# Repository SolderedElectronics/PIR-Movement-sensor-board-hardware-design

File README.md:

# PIR Movement sensor board Hardware Design

## About the Product

|  |
| :----------------------------------------------------------: |
| [Buy PIR Movement sensor board](https://www.solde.red/333083) |

A PIR (passive infrared) motion sensor is a device that detects physical movement within its field of vision by sensing changes in infrared radiation. This sensor works on the principle of detecting thermal thermal signals emitted by objects, mainly warm-blooded creatures like humans. The “passive” in the name refers to the fact that the sensor itself does not emit or radiate any energy for detection.

Easily connects to Dasduino/Arduino via digital pin. When it detects movement, it sets the output digital pin to HIGH. The angle that the sensor “sees” is 100 degrees and reaches up to 5 meters. It has a potentiometer for delay (how often to check for movement).

It is often used in a variety of applications, including home security systems, automatic lighting, and energy management, among others.

---

## Repository Contents

This repository contains all design files for PIR Movement sensor board, organized as follows:

- **`CAD` folder**: Contains KiCAD design files, including:
  - Schematics
  - PCB layout
  - Panel PCB layout
  - Source 3D files in Fusion360, if any
  - All files are sorted by version with a detailed change log.
- **`OUTPUTS` folder**: Includes all production-ready files, such as:
  - Bill of Materials (BOM) and interactive BOM (iBOM)
  - PDF versions of schematics
  - 3D `.step` file of the board
  - 3D-printable models
  - Gerber files for PCB manufacturing
  - Image of the pinout of the board
  - Product image
  - Compliance, legal and generic sales documents

Refer to the `Change Log` in the CAD folder for details about updates between versions.

---

## Learn More About the Product

Beyond the repository, explore the following resources:

### Soldered Verify

The **Soldered Verify** system ensures every board you purchase from Soldered is fully functional. It also provides access to exclusive test data for your product. To get started, find the unique Soldered Verify ID on your product's packaging and enter the ID on the [Soldered Verify page](https://soldered.com/verify/) to access test results and additional product details.

### Soldered Community

Soldered Community is your go-to place for technical support. Our engineers track and answer all questions posted there, and it’s a great space for the maker community. Get answers to your questions and solutions for your challenges at [Soldered Community](https://soldered.com/community).

### solde.red

solde.red is an ultimate URL shortener and information hub. Access it by typing solde.red/ followed by your product SKU, e.g., [solde.red/333000](https://solde.red/333000), to find getting-started guides, datasheets, open-source hardware and software files, certifications, images, pinouts, and more. Read more about the shortener [here](https://solde.red/info/).

---

## Contributing

Contributions are welcome! Here’s how you can get involved:

- Submit pull requests to enhance the design or fix issues.
- Report bugs or problems by opening an issue.

We encourage community collaboration to make this product even better.

---

## About Soldered

[Soldered for Makers](https://soldered.com) specializes in designing and manufacturing electronic products tailored for enthusiasts, ranging from hobbyists to professionals. Our portfolio includes electronic boards, sensors, and actuators that are widely utilized in fields such as microelectronics, mechatronics, robotics, programming, and IoT. Every product we offer is designed in-house and built upon open-source hardware and software platforms. Proudly certified and manufactured within the European Union, our catalog likely includes the product you need for your project.

We complement these products with comprehensive tutorials and manuals, product descriptions, schematics, programming codes, and project examples. Our round-the-clock [customer and technical support](https://soldered.com/community) is available for all our products, irrespective of the sales channel. Soldered’s success and services reflect our maker community’s unwavering [trust](https://www.trustpilot.com/review/soldered.com), for which we are deeply grateful. Join our community and create using Soldered products.

---

## License

All Soldered open-source hardware (OSH) is under The TAPR Open Hardware License. Read more in the LICENSE file located in this repository.

**Disclaimer:**

No warranty - all designs in this repository are distributed in the hope that they will be useful, but without any warranty. They are provided "AS IS", therefore without warranty of any kind, either expressed or implied. The entire quality and performance of what you do with the contents of this repository are your responsibility. In no event Soldered Electronics will be liable for your damages, or losses, including any general, special, incidental, or consequential damage arising out of the use or inability to use the contents of this repository. 

---

## Have fun!

Thank you for your support from your fellow makers at Soldered Electronics.

Happy Making!

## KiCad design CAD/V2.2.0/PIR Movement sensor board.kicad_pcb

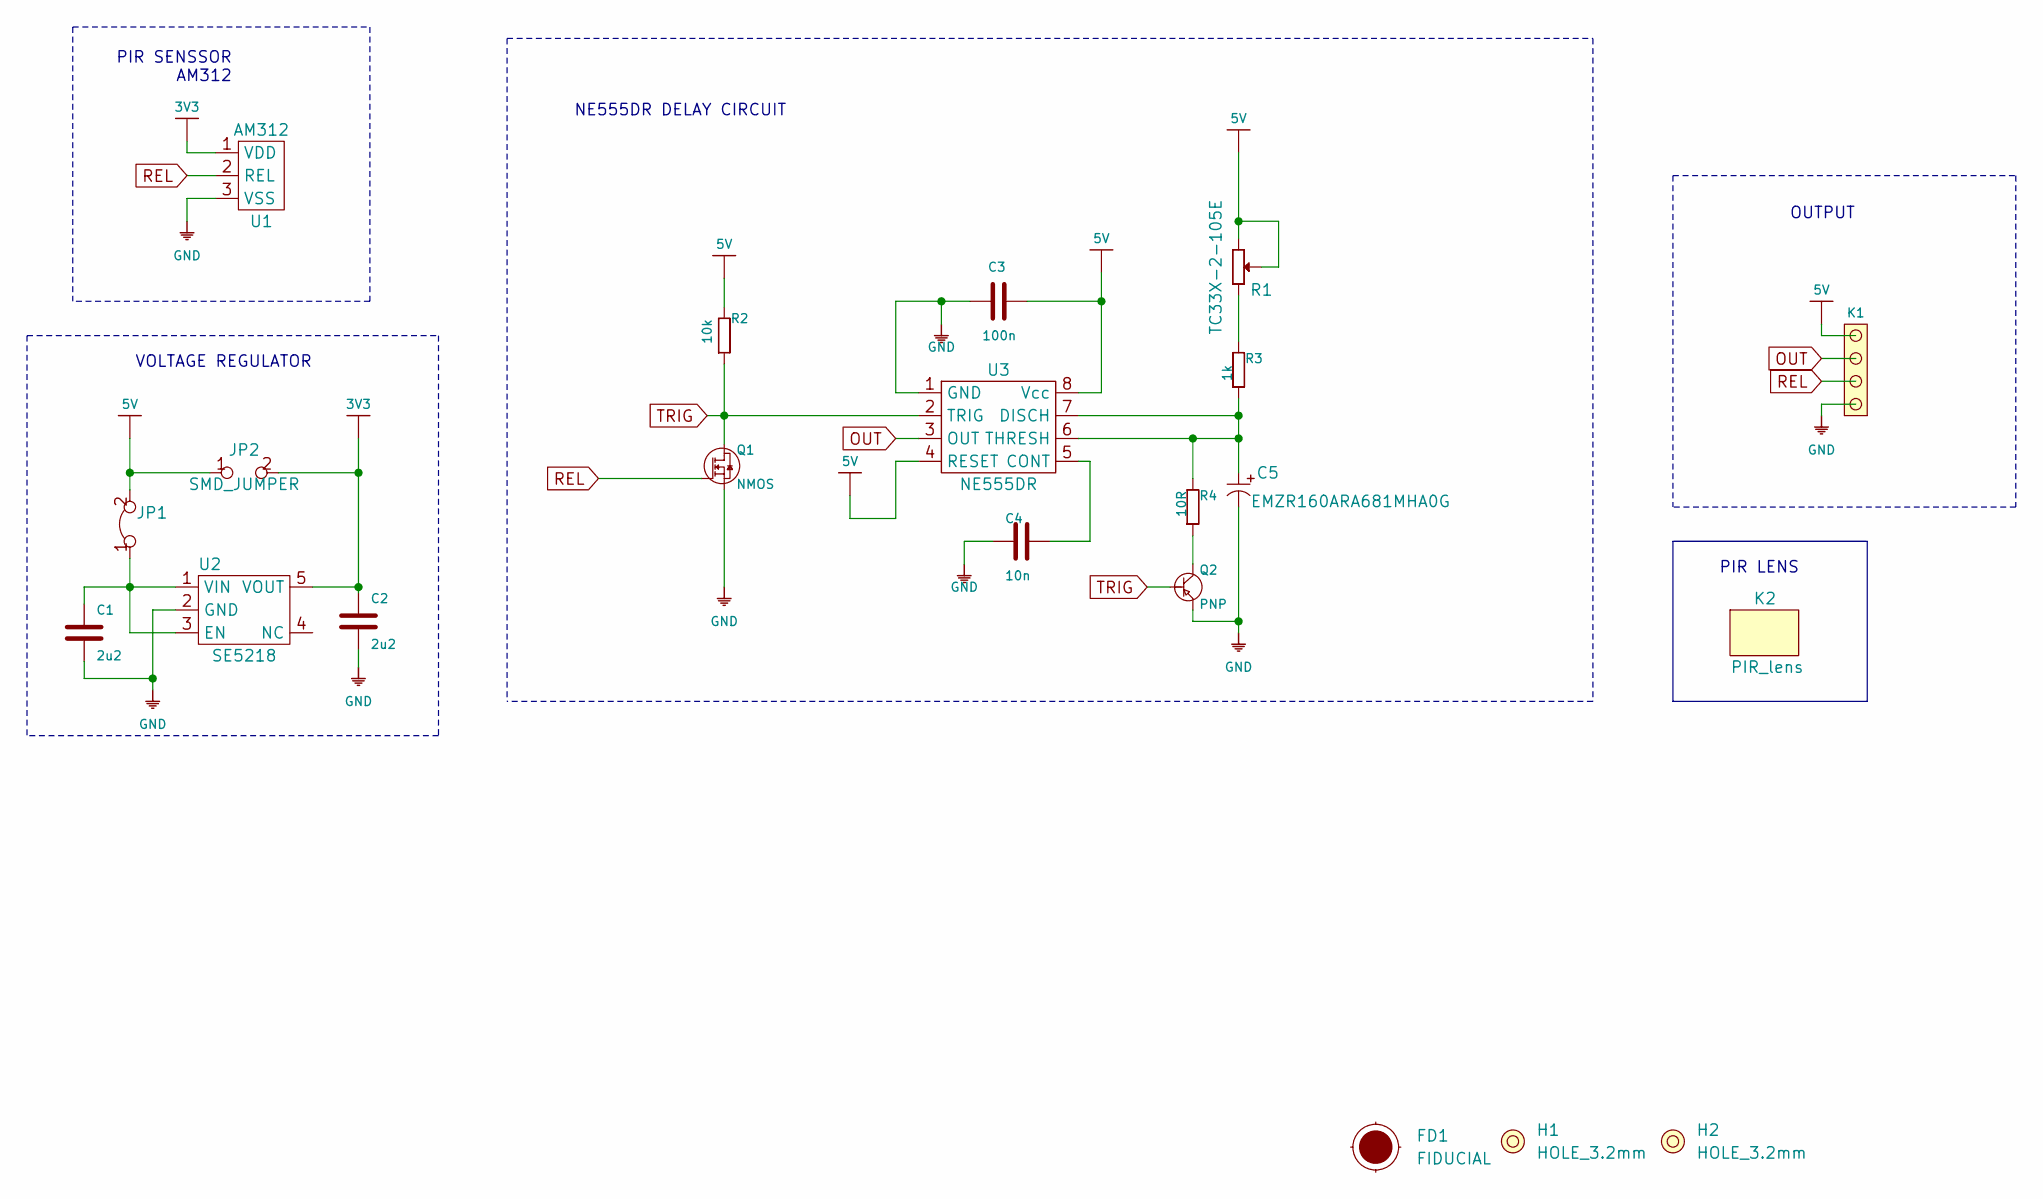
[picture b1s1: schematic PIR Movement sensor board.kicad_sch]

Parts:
C1, C2: 2u2; 0603C
C3: 100n; 0603C
C4: 10n; 0603C
C5: EMZR160ARA681MHA0G; ELECTROLITIC_CAP_8x8x14.5
FD1: FIDUCIAL; FIDUCIAL_23
H1, H2: HOLE_3.2mm
JP1: SMD-JUMPER-CONNECTED_TRACE_SLODERMASK
JP2: SMD_JUMPER
K1: HEADER_MALE_4X1
K2: PIR_lens; PIR_senzor_kapica
Q1: NMOS; SOT-23-3
Q2: PNP; SOT-23-3
R1: TC33X-2-105E; tc33x-2-103e
R2: 10k; 0603R
R3: 1k; 0603R
R4: 10R; 0603R
U1: AM312; PIR_senzor
U2: SE5218; SOT-23-5
U3: NE555DR; SOIC−8

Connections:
3V3: C2.2, JP2.2, U1.1 (VDD), U2.5 (VOUT)
5V: C3.1, JP1.2, JP2.1, K1.4, R1.2, R1.3, R2.2, U3.4 (RESET), U3.8 (Vcc)
GND: C1.1, C2.1, C3.2, C4.2, C5.2 (-), K1.1, Q1.2 (S), Q2.2 (E), U1.3 (VSS), U2.2 (GND), U3.1 (GND)
unnamed: C1.2, JP1.1, U2.1 (VIN), U2.3 (EN)
unnamed: C4.1, U3.5 (CONT)
unnamed: C5.1 (+), R3.1, R4.2, U3.6 (THRESH), U3.7 (DISCH)
unnamed: Q2.3 (C), R4.1
unnamed: R1.1, R3.2
OUT: K1.3, U3.3 (OUT)
REL: K1.2, Q1.1 (G), U1.2 (REL)
TRIG: Q1.3 (D), Q2.1 (B), R2.1, U3.2 (TRIG)

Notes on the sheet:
NE555DR DELAY CIRCUIT
OUTPUT
VOLTAGE REGULATOR
PIR LENS
PIR SENSSOR AM312

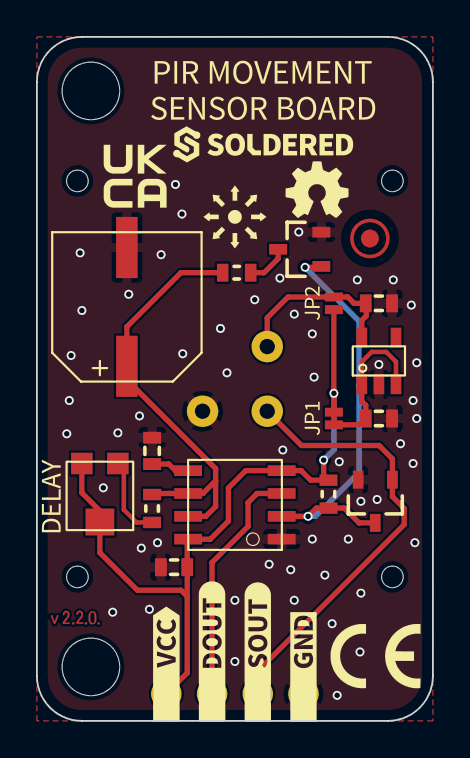
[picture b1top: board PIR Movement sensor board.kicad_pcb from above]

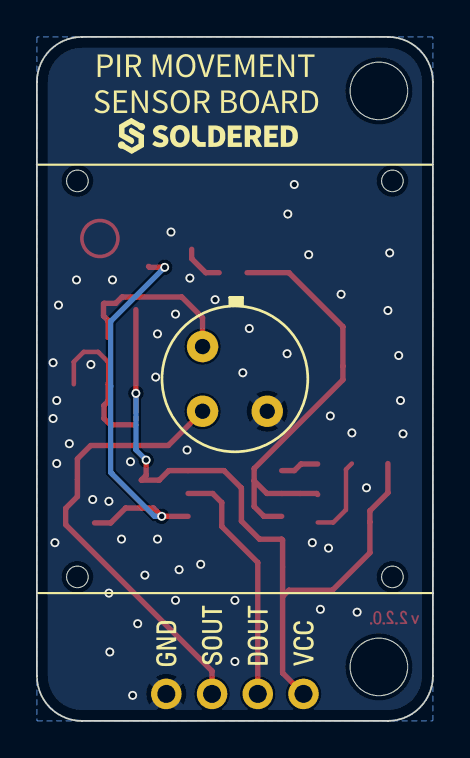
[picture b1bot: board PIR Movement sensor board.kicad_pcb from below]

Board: 2 copper layers, 22.0 x 38.0 mm, 36 parts (8 on the bottom side), 11 nets.

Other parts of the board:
kibuzzard-63F87DE8, kibuzzard-63F87DE8#2: G***; kibuzzard-63F87DE8
kibuzzard-63F87DF0, kibuzzard-63F87DF0#2: G***; kibuzzard-63F87DF0
kibuzzard-63F87E9A: G***; kibuzzard-63F87E9A
kibuzzard-63F87E62: G***; kibuzzard-63F87E62
kibuzzard-63F87E82: G***; kibuzzard-63F87E82
kibuzzard-63F87F2A: G***; kibuzzard-63F87F2A
kibuzzard-63F87FB1: G***; kibuzzard-63F87FB1
kibuzzard-63F87FDE: G***; kibuzzard-63F87FDE
kibuzzard-63F882D0: G***; kibuzzard-63F882D0
kibuzzard-63F8825B: G***; kibuzzard-63F8825B
kibuzzard-63F8828A: G***; kibuzzard-63F8828A
kibuzzard-63F88249: G***; kibuzzard-63F88249
kibuzzard-63F88265: G***; kibuzzard-63F88265

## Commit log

2022-08-06 Updating open source files.
